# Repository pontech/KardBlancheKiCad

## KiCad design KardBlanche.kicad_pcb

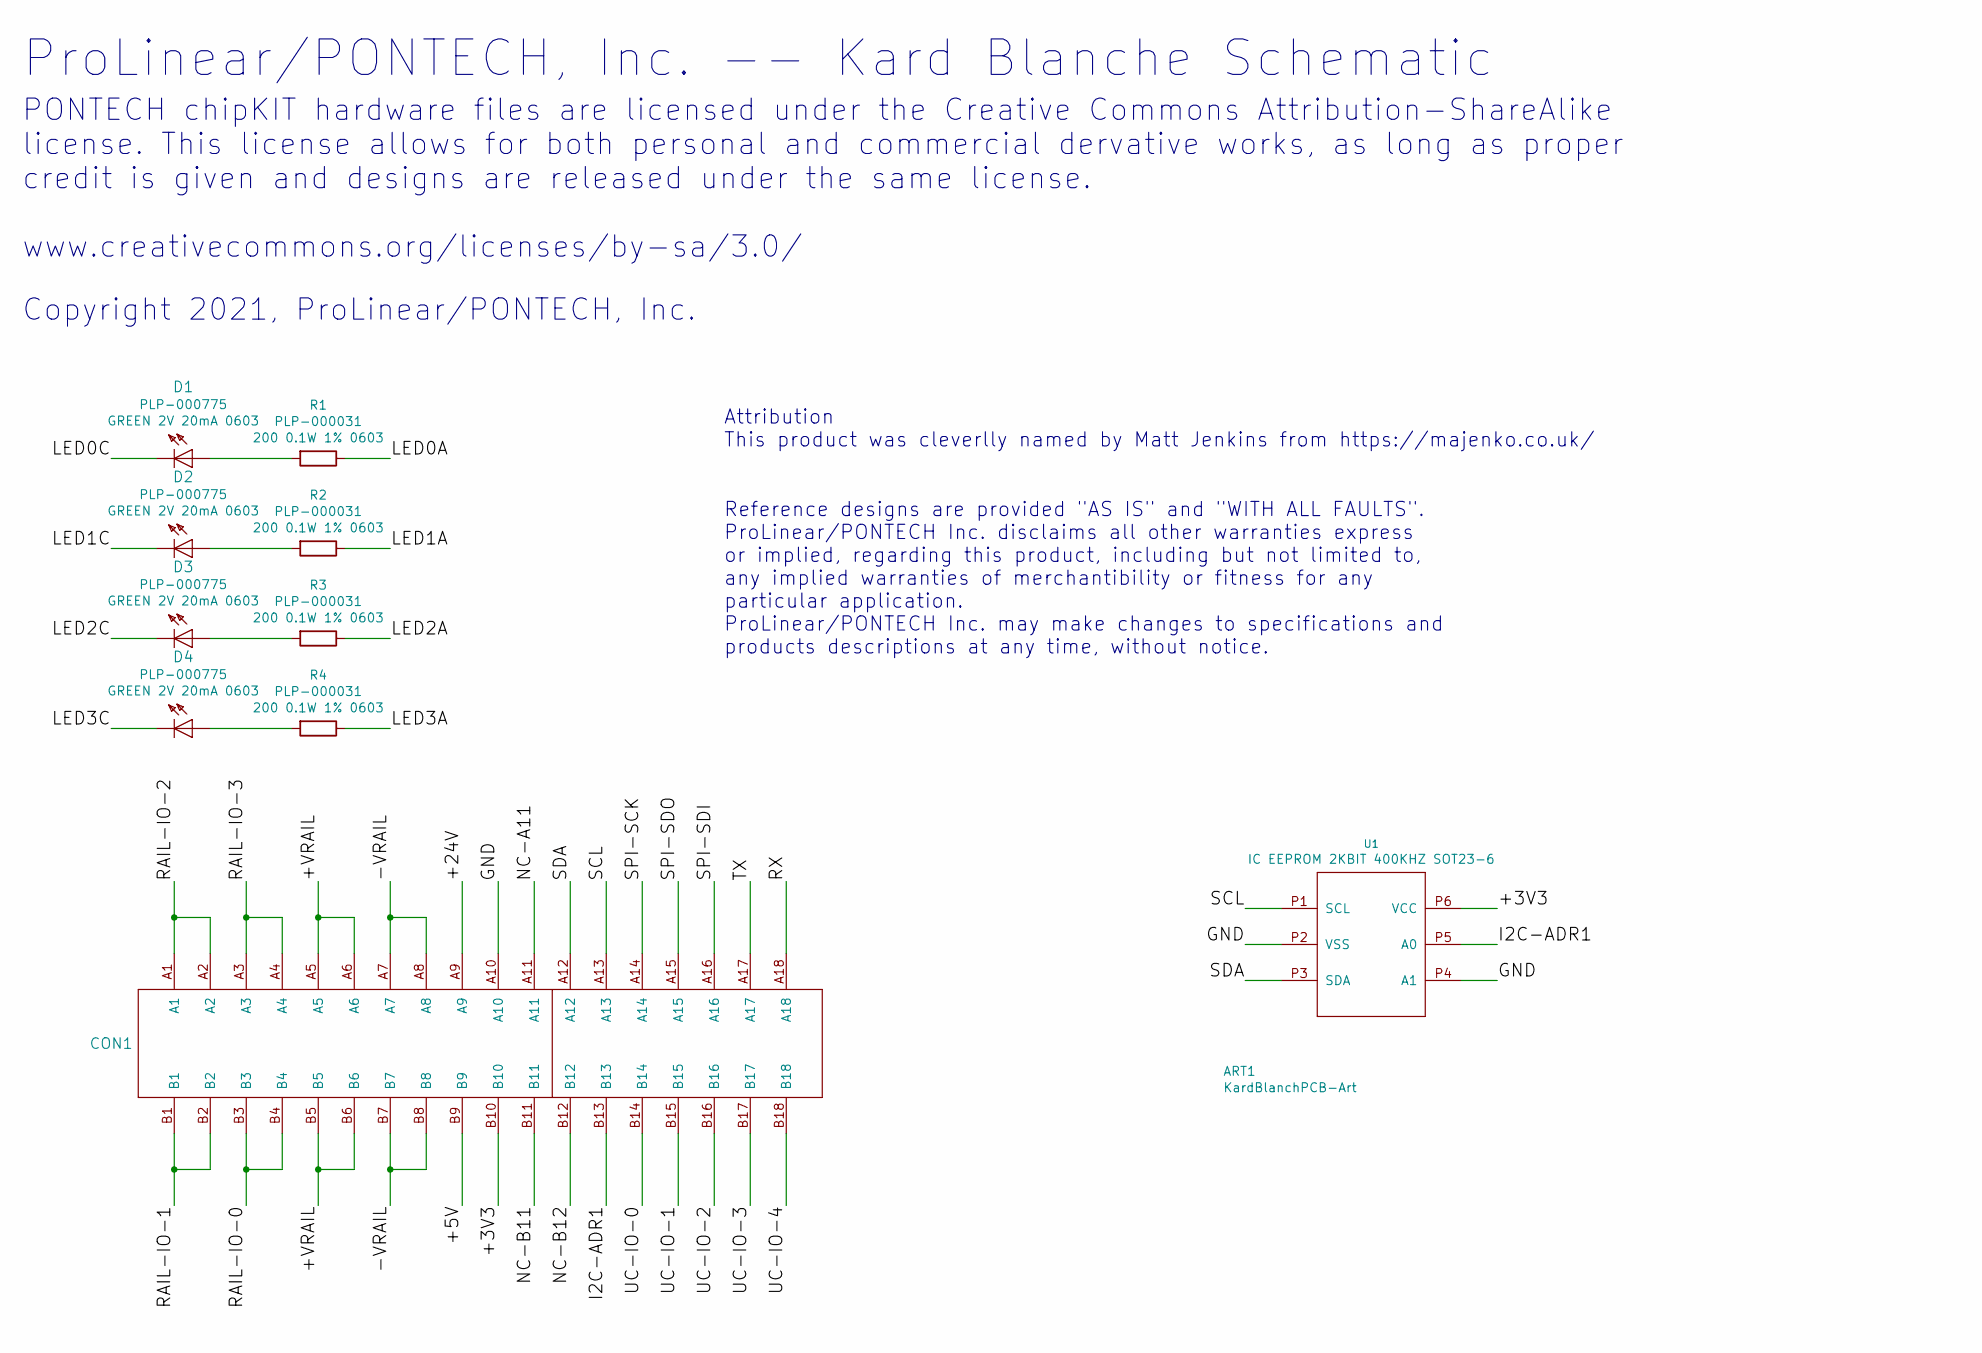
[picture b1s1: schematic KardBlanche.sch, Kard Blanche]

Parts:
ART1: KardBlanchPCB-Art; KardBlanchePCB-Art
CON1: PLPA-0105
D1, D2, D3, D4: PLP-000775
R1, R2, R3, R4: PLP-000031; R_0603_1608Metric
U1: PLP-000898; SOT23-6

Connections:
/+3V3: CON1.B10, U1.P6 (VCC)
/+5V: CON1.B9
/+24V: CON1.A9
/+VRAIL: CON1.A5, CON1.A6, CON1.B5, CON1.B6
/-VRAIL: CON1.A7, CON1.A8, CON1.B7, CON1.B8
/GND: CON1.A10, U1.P2 (VSS), U1.P4 (A1)
/I2C-ADR1: CON1.B13, U1.P5 (A0)
/LED0A: R1.1
/LED0C: D1.C
/LED1A: R2.1
/LED1C: D2.C
/LED2A: R3.1
/LED2C: D3.C
/LED3A: R4.1
/LED3C: D4.C
/NC-A11: CON1.A11
/NC-B11: CON1.B11
/NC-B12: CON1.B12
/RAIL-IO-0: CON1.B3, CON1.B4
/RAIL-IO-1: CON1.B1, CON1.B2
/RAIL-IO-2: CON1.A1, CON1.A2
/RAIL-IO-3: CON1.A3, CON1.A4
/RX: CON1.A18
/SCL: CON1.A13, U1.P1 (SCL)
/SDA: CON1.A12, U1.P3 (SDA)
/SPI-SCK: CON1.A14
/SPI-SDI: CON1.A16
/SPI-SDO: CON1.A15
/TX: CON1.A17
/UC-IO-0: CON1.B14
/UC-IO-1: CON1.B15
/UC-IO-2: CON1.B16
/UC-IO-3: CON1.B17
/UC-IO-4: CON1.B18
unnamed: D1.A, R1.2
unnamed: D2.A, R2.2
unnamed: D3.A, R3.2
unnamed: D4.A, R4.2

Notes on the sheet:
ProLinear/PONTECH, Inc. -- Kard Blanche Schematic
PONTECH chipKIT hardware files are licensed under the Creative Commons Attribution-ShareAlike license. This license allows for both personal and commercial dervative works, as long as proper credit is given and designs are released under the same license. www.creativecommons.org/licenses/by-sa/3.0/
Copyright 2021, ProLinear/PONTECH, Inc.
Attribution This product was cleverlly named by Matt Jenkins from https://majenko.co.uk/
Reference designs are provided "AS IS" and "WITH ALL FAULTS". ProLinear/PONTECH Inc. disclaims all other warranties express or implied, regarding this product, including but not limited to, any implied warranties of merchantibility or fitness for any particular application. ProLinear/PONTECH Inc. m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

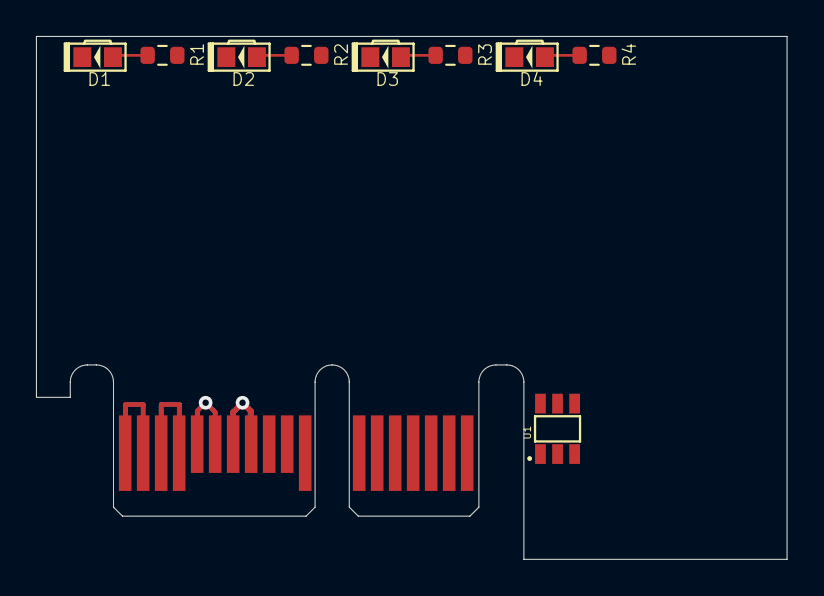
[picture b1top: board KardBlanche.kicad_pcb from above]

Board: 2 copper layers, 41.7 x 29.0 mm, 11 parts (0 on the bottom side), 15 nets.

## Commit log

2021-12-12 Initial command REV-A
2021-12-12 Added REV-A Schematic to documentation
